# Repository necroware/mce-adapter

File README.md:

# MCE Adapter (Prototype!)

The MCA-Adapter is a device, which can convert MDA (and Hercules), EGA and CGA
to analogue RGBS signal. It supports following features.

- Converts digital MDA, Hercules, CGA and EGA to analog RGBS or RGBHV/VGA signal
- Color DAC for 3, 4, 16 and 64 color modes
- Switchable composite sync from H- and V-Sync
- Loop through HV-Sync, colors conversion only mode
- Includes IBM's "brown-hack"for CGA and 16-colors EGA modes
- Hi/Low resolution EGA mode autodect for proper color representation
- Switchable green, white and amber monochrome screen emulation

Youtube Videos:
- Part 1: Why GBS-8200 is not a CGA/EGA converter https://youtu.be/7c3yLX52ZEs
- Part 2: Theory and implementation https://youtu.be/aUFKB4b5KpE
- Part 3: Showtime https://youtu.be/F1685u-QQ0k

## Why did I make this?

Because why not? I wanted to get some practice with EDA and I needed such an
adapter to test some of my old graphics cards.

## Why might somebody need this?

If you want to connect your old PC with MDA, CGA or EGA graphics to a more
modern VGA display, it's going to be difficult. First of all, this old graphics
standards are digital, so RGB information is sent as a bunch of 1 and 0. VGA on
the other hand understands only analogue signals, so f.e. the intensity of the red
color is defined by some value between two voltages and not by a discrete value.
So the first job of this adapter is to translates digital video signals into
analogue video signals. However, this is may be not enough, since the horizontal
sync signal of the old video standards is not supported by a usual VGA monitor.
For this purpose, a very famous upscaler named GBS-8200 and compatible can be
used to convert the sync signal to VGA compatible level.  However, GBS-8200
expects such called composite sync signal, where horizontal and vertical sync
signals are combined. This is, where this adapter comes into place, it doesn't
only convert digital RGB signal to analogue, but also composite sync signal from
incoming horizontal and vertical signals. Long story short, you will need this
adapter to connect a MDA, CGA or EGA graphics card to an analogue RGB monitor,
either by using GBS-8200 converter or the adapter standalone, in case your
monitor supports horizontal frequencies down to 15kHz.

## Why didn't I take an existing solution?

Well, first of all, I wanted to gain some experience in this. Second, I actually
was heavily inspired by a YouTube video by TheRasteri, where he evaluates the
output possibilities of an old PC, talks about the technical background and
creates his own adapter. You can see the video here:

* Part 1: https://www.youtube.com/watch?v=kHhpTq-WSJk
* Part 2: https://www.youtube.com/watch?v=vwKA1z8tg1g

As I saw his solution with a ROM, I instantly thought, that the same thing can
be done using a programmable logic IC, like GAL16V8. It would have some benefits
in timing behaviour over a solution with ROM and be also very flexible. So, here
it is.

## Which modes does it support?

The adapter can convert MDA, Hercules, CGA, 16 colors EGA and 64 colors EGA to
standard VGA (RGBHV) or RGBS (combined HV-sync). The sync output frequency is
always the same as the input frequency. The adapter can only compose HV-sync,
but doesn't actively change it. The digital color signal is converted to analogue
color signal, so any analogue RGB monitor should understand it.

## Jumpers and switches

ATTENTION: Jumper settings changed compared to previous revisions 

Color mode selection J1:
Mode                       | 1-2 | 3-4 
---------------------------|-----|-----
CGA/EGA (15kHz / 21kHz)    | OFF | OFF 
MDA/Hercules white (18kHz) | ON  | ON
MDA/Hercules green (18kHz) | ON  | OFF
MDA/Hercules amber (18kHz) | OFF | ON

Sync selectiom J2:
Mode               | Setting
-------------------|----------
HV-Sync (VGA)      | 1-2
C-Sync (Composite) | 2-3

## How to use this stuff?

1. Take the gerber files and make a PCB.
2. Assemble the board
3. Compile code/mceplug.eqn using EQN2JED tool
4. Write the compiled jed file to a GAL16V8 IC
5. Put it into the board and connect the cables
   f.e. CGA -> MCE Adapter -> GBS-8200 -> Analog RGB Monitor

## Bill of materials

Reference  |#  |LCSC    |Description
-----------|---|--------|-------------------------------------
C1 C2      |2  |C472888 |capacitor 4.7µF
D1         |1  |C402218 |diode 1N5819
H1         |1  |C492405 |pin header 1x6
J1         |1  |C492419 |pin header 2x2
J2         |1  |C429954 |pin header 1x3
PWR1       |1  |C46398  |USB-B mini port
PWR2       |1  |C152154 |pin header 1x2 (+5V connector)
R1 R2      |2  |C713968 |resistor 33 Ohm
R3 R5 R7   |3  |C2848597|resistor 1.3k Ohm
R4 R6 R8   |3  |C119320 |resistor 680 Ohm
R9         |1  |C173139 |resistor 10k Ohm
U1         |1  |C6509   |GAL16V8B (or compatible)
VIDEO_IN1  |1  |C141882 |DB9 female connector (MDA/EGA/CGA)
VIDEO_OUT1 |1  |C75754  |DIB15 female connector (VGA)

## Tested with following monitors
- GBS-8200 with original hardware (only 15kHz modes work)
- GBS-8200 with gbs-control firmaware (Hercules and hi-res EGA sync unstable)
- NEC Multisync LCD1970NX 19" TFT (everything works fine, Hercules is not in full screen, but works stable)
- EIZO L365 15" TFT (only Hi-Res EGA works, doesn't support 15kHz CGA nor 50Hz Hercules)
- Benq BL702A

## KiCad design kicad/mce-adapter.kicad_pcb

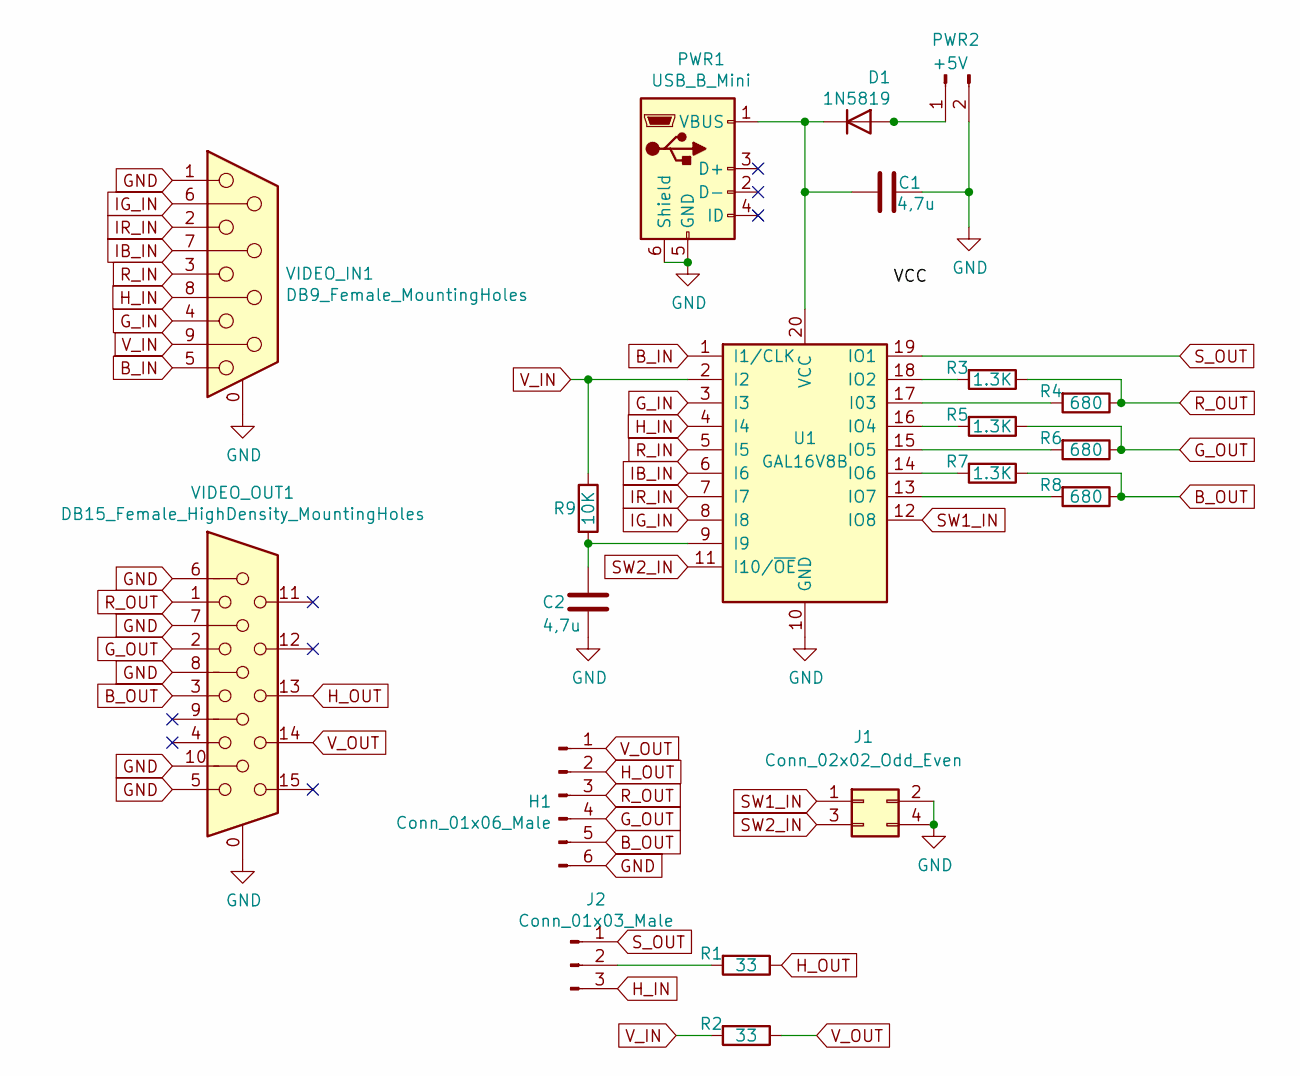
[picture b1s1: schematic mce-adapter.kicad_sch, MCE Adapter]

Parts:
C1, C2: 4,7u; C_Disc_D5.0mm_W2.5mm_P5.00mm; LCSC C472888
D1: 1N5819; D_DO-34_SOD68_P7.62mm_Horizontal; LCSC C402218
H1: Conn_01x06_Male; PinHeader_1x06_P2.54mm_Vertical; LCSC C492405
J1: Conn_02x02_Odd_Even; PinHeader_2x02_P2.54mm_Vertical; LCSC C492419
J2: Conn_01x03_Male; PinHeader_1x03_P2.54mm_Vertical; LCSC C429954
PWR1: USB_B_Mini; USB_Mini-B-Jing_Extension_LSCS_C46398; LCSC C46398
PWR2: +5V; PinHeader_1x02_P2.54mm_Vertical; LCSC C152154
R1, R2: 33; R_Axial_DIN0204_L3.6mm_D1.6mm_P7.62mm_Horizontal; LCSC C713968
R3, R5, R7: 1.3K; R_Axial_DIN0204_L3.6mm_D1.6mm_P7.62mm_Horizontal; LCSC C2848597
R4, R6, R8: 680; R_Axial_DIN0204_L3.6mm_D1.6mm_P7.62mm_Horizontal; LCSC C119320
R9: 10K; R_Axial_DIN0204_L3.6mm_D1.6mm_P7.62mm_Horizontal; LCSC C173139
U1: GAL16V8B; DIP-20_W7.62mm_Socket; LCSC C6509
VIDEO_IN1: DB9_Female_MountingHoles; DSUB-9_Female_Horizontal_P2.77x2.84mm_EdgePinOffset7.70mm_H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; LCSC C141882
VIDEO_OUT1: DB15_Female_HighDensity_MountingHoles; DSUB-15-HD_Female_Horizontal_P2.29x1.98mm_EdgePinOffset8.35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; LCSC C75754

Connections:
B_IN: U1.1 (I1/CLK), VIDEO_IN1.5
B_OUT: H1.5, R7.1, R8.1, VIDEO_OUT1.3
GND: C1.2, C2.2, H1.6, J1.2, J1.4, PWR1.5 (GND), PWR1.6 (Shield), PWR2.2, U1.10 (GND), VIDEO_IN1.0 (PAD), VIDEO_IN1.1, VIDEO_OUT1.0, VIDEO_OUT1.5, VIDEO_OUT1.6, VIDEO_OUT1.7, VIDEO_OUT1.8, VIDEO_OUT1.10
G_IN: U1.3 (I3), VIDEO_IN1.4
G_OUT: H1.4, R5.1, R6.1, VIDEO_OUT1.2
H_IN: J2.3, U1.4 (I4), VIDEO_IN1.8
H_OUT: H1.2, R1.1, VIDEO_OUT1.13
IB_IN: U1.6 (I6), VIDEO_IN1.7
IG_IN: U1.8 (I8), VIDEO_IN1.6
IR_IN: U1.7 (I7), VIDEO_IN1.2
unnamed: D1.2 (A), PWR2.1
unnamed: C1.1, D1.1 (K), PWR1.1 (VBUS), U1.20 (VCC)
unnamed: J2.2, R1.2
unnamed: R4.2, U1.17 (I03)
unnamed: C2.1, R9.2, U1.9 (I9)
unnamed: R3.2, U1.18 (IO2)
unnamed: R5.2, U1.16 (IO4)
unnamed: R6.2, U1.15 (IO5)
unnamed: R7.2, U1.14 (IO6)
unnamed: R8.2, U1.13 (IO7)
R_IN: U1.5 (I5), VIDEO_IN1.3
R_OUT: H1.3, R3.1, R4.1, VIDEO_OUT1.1
SW1_IN: J1.1, U1.12 (IO8)
SW2_IN: J1.3, U1.11 (I10/~OE)
S_OUT: J2.1, U1.19 (IO1)
V_IN: R2.2, R9.1, U1.2 (I2), VIDEO_IN1.9
V_OUT: H1.1, R2.1, VIDEO_OUT1.14

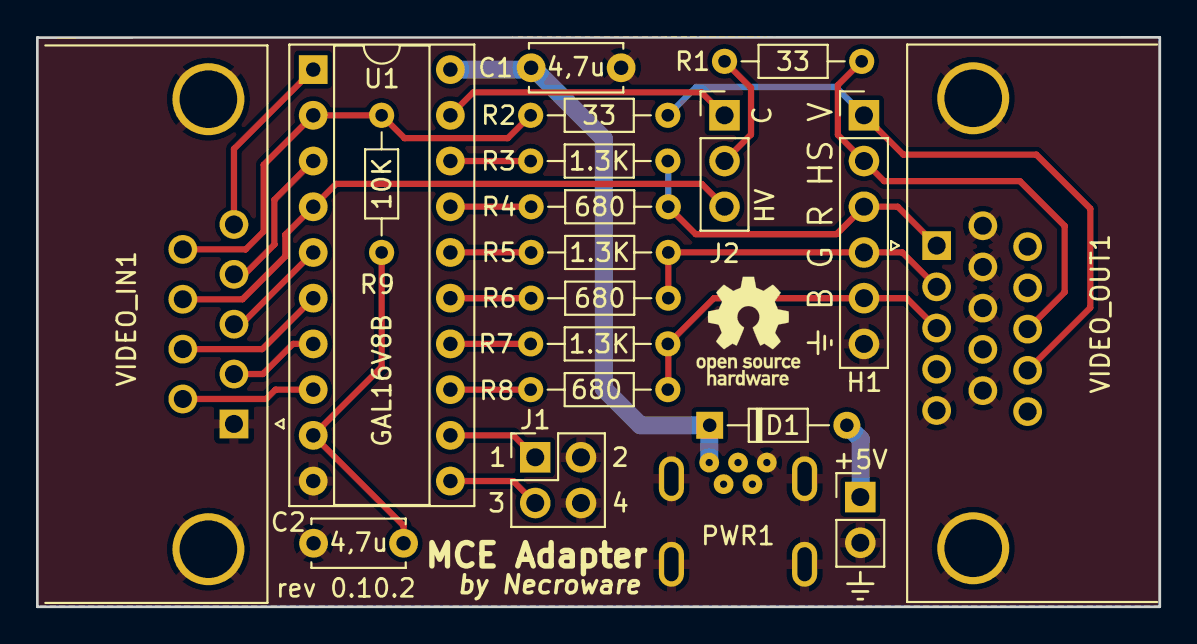
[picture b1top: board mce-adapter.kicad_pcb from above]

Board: 2 copper layers, 62.4 x 31.6 mm, 20 parts (0 on the bottom side), 27 nets.

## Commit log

2020-10-15 Initial readme
2020-10-15 Added rev0.5
2020-10-15 Add revision 0.6
2020-10-16 Add image of the schema
2020-10-16 Moved all gerber files into a zip archive
2020-11-23 Switched to KiCad and regenerated output
2020-11-23 Move gerber folder into kicad subfolder
2020-11-23 Add necroware kicad library
2020-11-23 Regenrated gerber files
2020-11-23 Vastly shrink PCB
2020-11-23 Move USB slightly over the edge
2020-11-23 Update LSCS part number
2020-11-25 Update LCSC part numbers
2020-11-25 Fix the readme
2020-11-25 Update shim
2020-11-27 Set submodule url to necroware repos
2020-12-06 Reajust some resistors improve layout
2020-12-06 Update BOM
2020-12-08 Move parts away from VGA out.
    Add some back face silk notations
2020-12-08 Add on silk documentation
2020-12-08 Update pcb image
2020-12-08 Pull PWR1 from the edge inwards
2020-12-08 Regenerate gerber files
2021-02-03 Update README.md
    R8 does not need to be a 3W resistor. Standard 1/4W should be fine.
2021-02-05 Fix too short board under VGA output
2021-02-05 Remove the gerber files from the project.
    The gerber files will be deployed in release only
2021-02-06 Added tested monitors list
2021-03-25 Added video links
2021-03-25 Fixed video links
2021-03-25 Fixed video links, now really :)
2021-10-08 Add files via upload
    Add short and very short layout. Not tested yet, but should work. Both use PLCC Chip and vertical Resistors and Diode. Very short has no USB-Power, no RGBS function (so no need for sync polarity swit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
    It is designed to connect direct at a screen with gender changer (male-male) or 180° twisted male plug.
2021-10-09 Add RGBS option
    Add RGBS option with solder jumper and 2 SMD Resistors. DIP Switch was replace in 3D View.
2021-10-09 Extreme small to fit in a plug shell
    Only 14x22mm, can fit into a modified plug shell. Most small SMD, no RGBs
2021-10-09 picture of all small types
2021-10-10 improved Short = Shorter
    Move capacitor and resistors to shorter the full functional and not SMD board again
2024-01-29 Updated gitignore
2024-01-29 Readjusted resistor values, updated to version 0.7.2
2024-01-29 Switched to KiCad 7
2024-01-29 Fixed GAL name
2024-01-29 Re-added DIP switch, rev. 0.8.0
2024-01-29 Update image
2024-01-31 Added mode auto-detection
2024-02-13 Readjusted resistor networks to get blow 0.7V
2024-02-14 Update readme and LCSC parts
2024-03-14 Add a 3D model
2024-03-29 Updated project to KiKad 8.0
2025-02-04 fix: replace C2 with 4,7uF
2025-02-09 issue-15: reduce resistor values
2025-02-09 fix: simplify c-sync equation
    The c-sync equation was slightly complicated and was trying to
    incorporate the sync mode. The negative/positive v-sync level is
    used for color mode detection and c-sync is also inverted dependent
    on that. However, so far I didn't find hardware which would need that.
    That could be even wrong, so for now I removed the mode from the c-sync
    equation and it is again a simple XNOR, which hopefully will just work
2025-02-09 Try to improve amber colors.
    The code uses red and green chanels to emulate amber. In MDA/Hercules
    two bits are used to encode the color. The actual color bit and the
    intensity bit, so there can be theoretically 4 color shades: Black,
    Dark, Normal, Bright. However Hercules seems not to use the Dark shade,
    which could be forced by setting intensity bit only with color set to 0.
    I tested it with an original Hercules card and some clones as well.
